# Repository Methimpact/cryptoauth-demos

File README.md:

cryptoauth-demos
================

Demos of CryptoAuth Devices

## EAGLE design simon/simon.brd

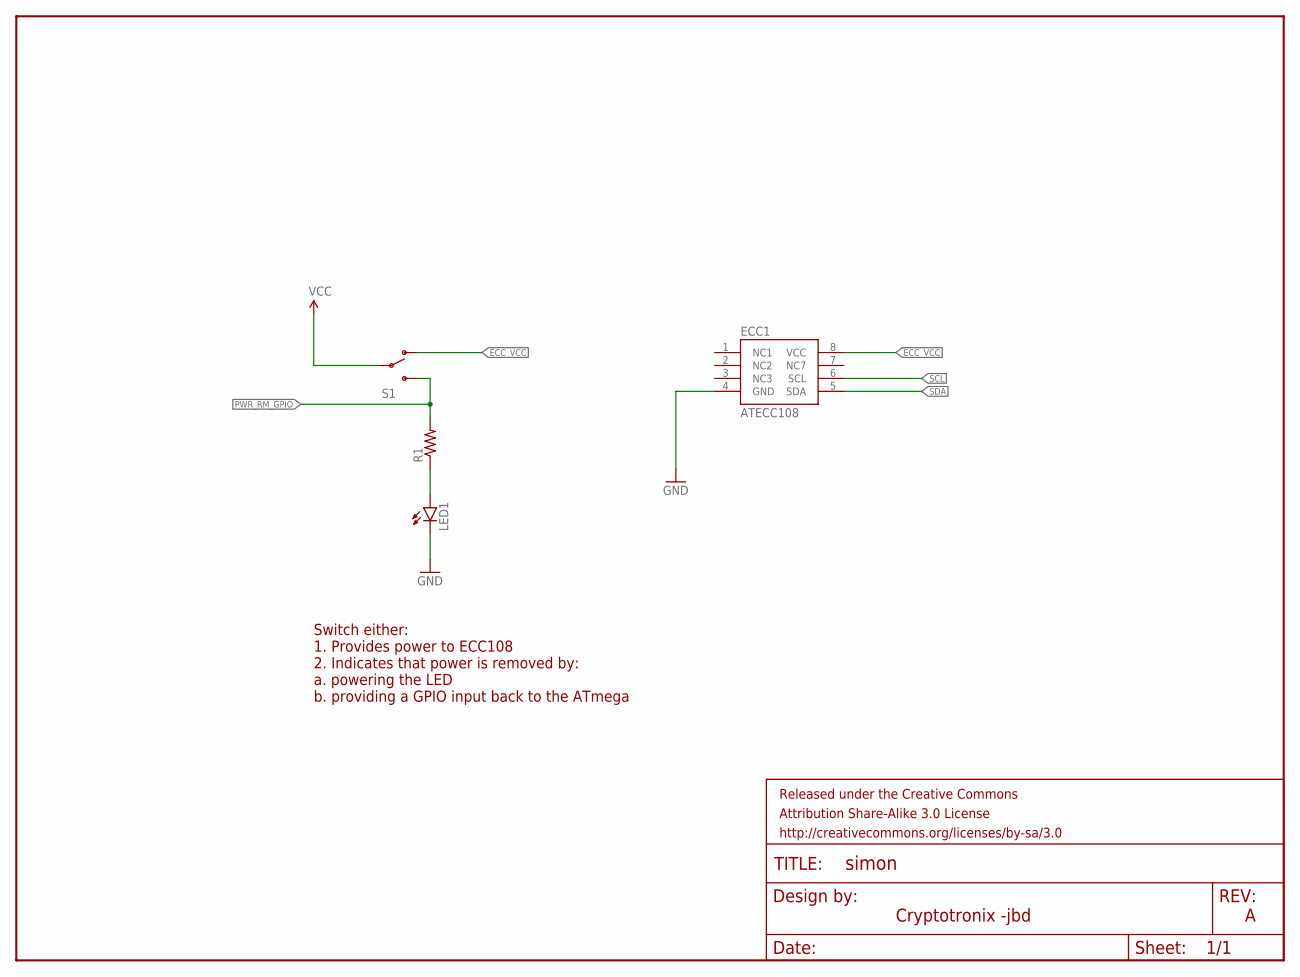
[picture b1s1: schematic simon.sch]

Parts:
ECC1: ATECC108; SOIC8
FRAME1: FRAME-LETTER; CREATIVE_COMMONS
LED1: LED0603; LED-0603
R1: RESISTOR0603; 0603-RES
S1: SWITCH-SPDT-SMD-A; SWITCH-SPST-SMD-A

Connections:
ECC_VCC: ECC1.8 (VCC), S1.1 (O)
GND: ECC1.4 (GND), LED1.C
unnamed: LED1.A, R1.1
PWR_RM_GPIO: R1.2, S1.3 (S)
SCL: ECC1.6 (SCL)
SDA: ECC1.5 (SDA)
VCC: S1.2

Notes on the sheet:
Cryptotronix -jbd
Switch either: 1. Provides power to ECC108 2. Indicates that power is removed by: a. powering the LED b. providing a GPIO input back to the ATmega

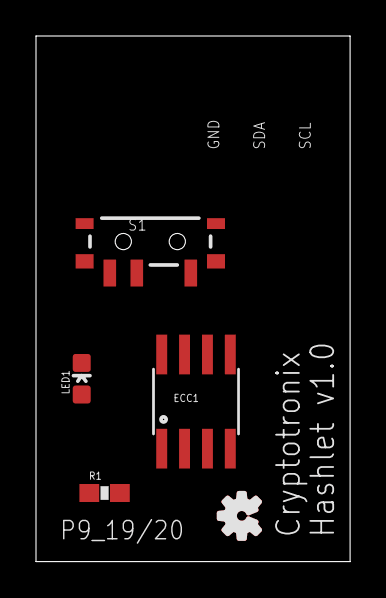
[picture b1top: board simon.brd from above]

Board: 2 copper layers, 17.4 x 29.2 mm, 5 parts (0 on the bottom side), 4 nets.

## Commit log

2014-11-22 initial
2014-12-08 Adds initial sketch.
2014-12-09 in progress
2014-12-10 Adds sending mac on addmove.
2014-12-11 Sunny day working.
2014-12-11 Removes commented code.
2015-01-03 moves file

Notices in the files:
parts and their libraries:
SparkFun-Aesthetics: Licensing: CC v3.0 Share-Alike You are welcome to use this library for commercial purposes.
SparkFun-Aesthetics: Released under the Creative Commons Attribution Share-Alike 3.0 License
SparkFun-Aesthetics: http://creativecommons.org/licenses/by-sa/3.0
